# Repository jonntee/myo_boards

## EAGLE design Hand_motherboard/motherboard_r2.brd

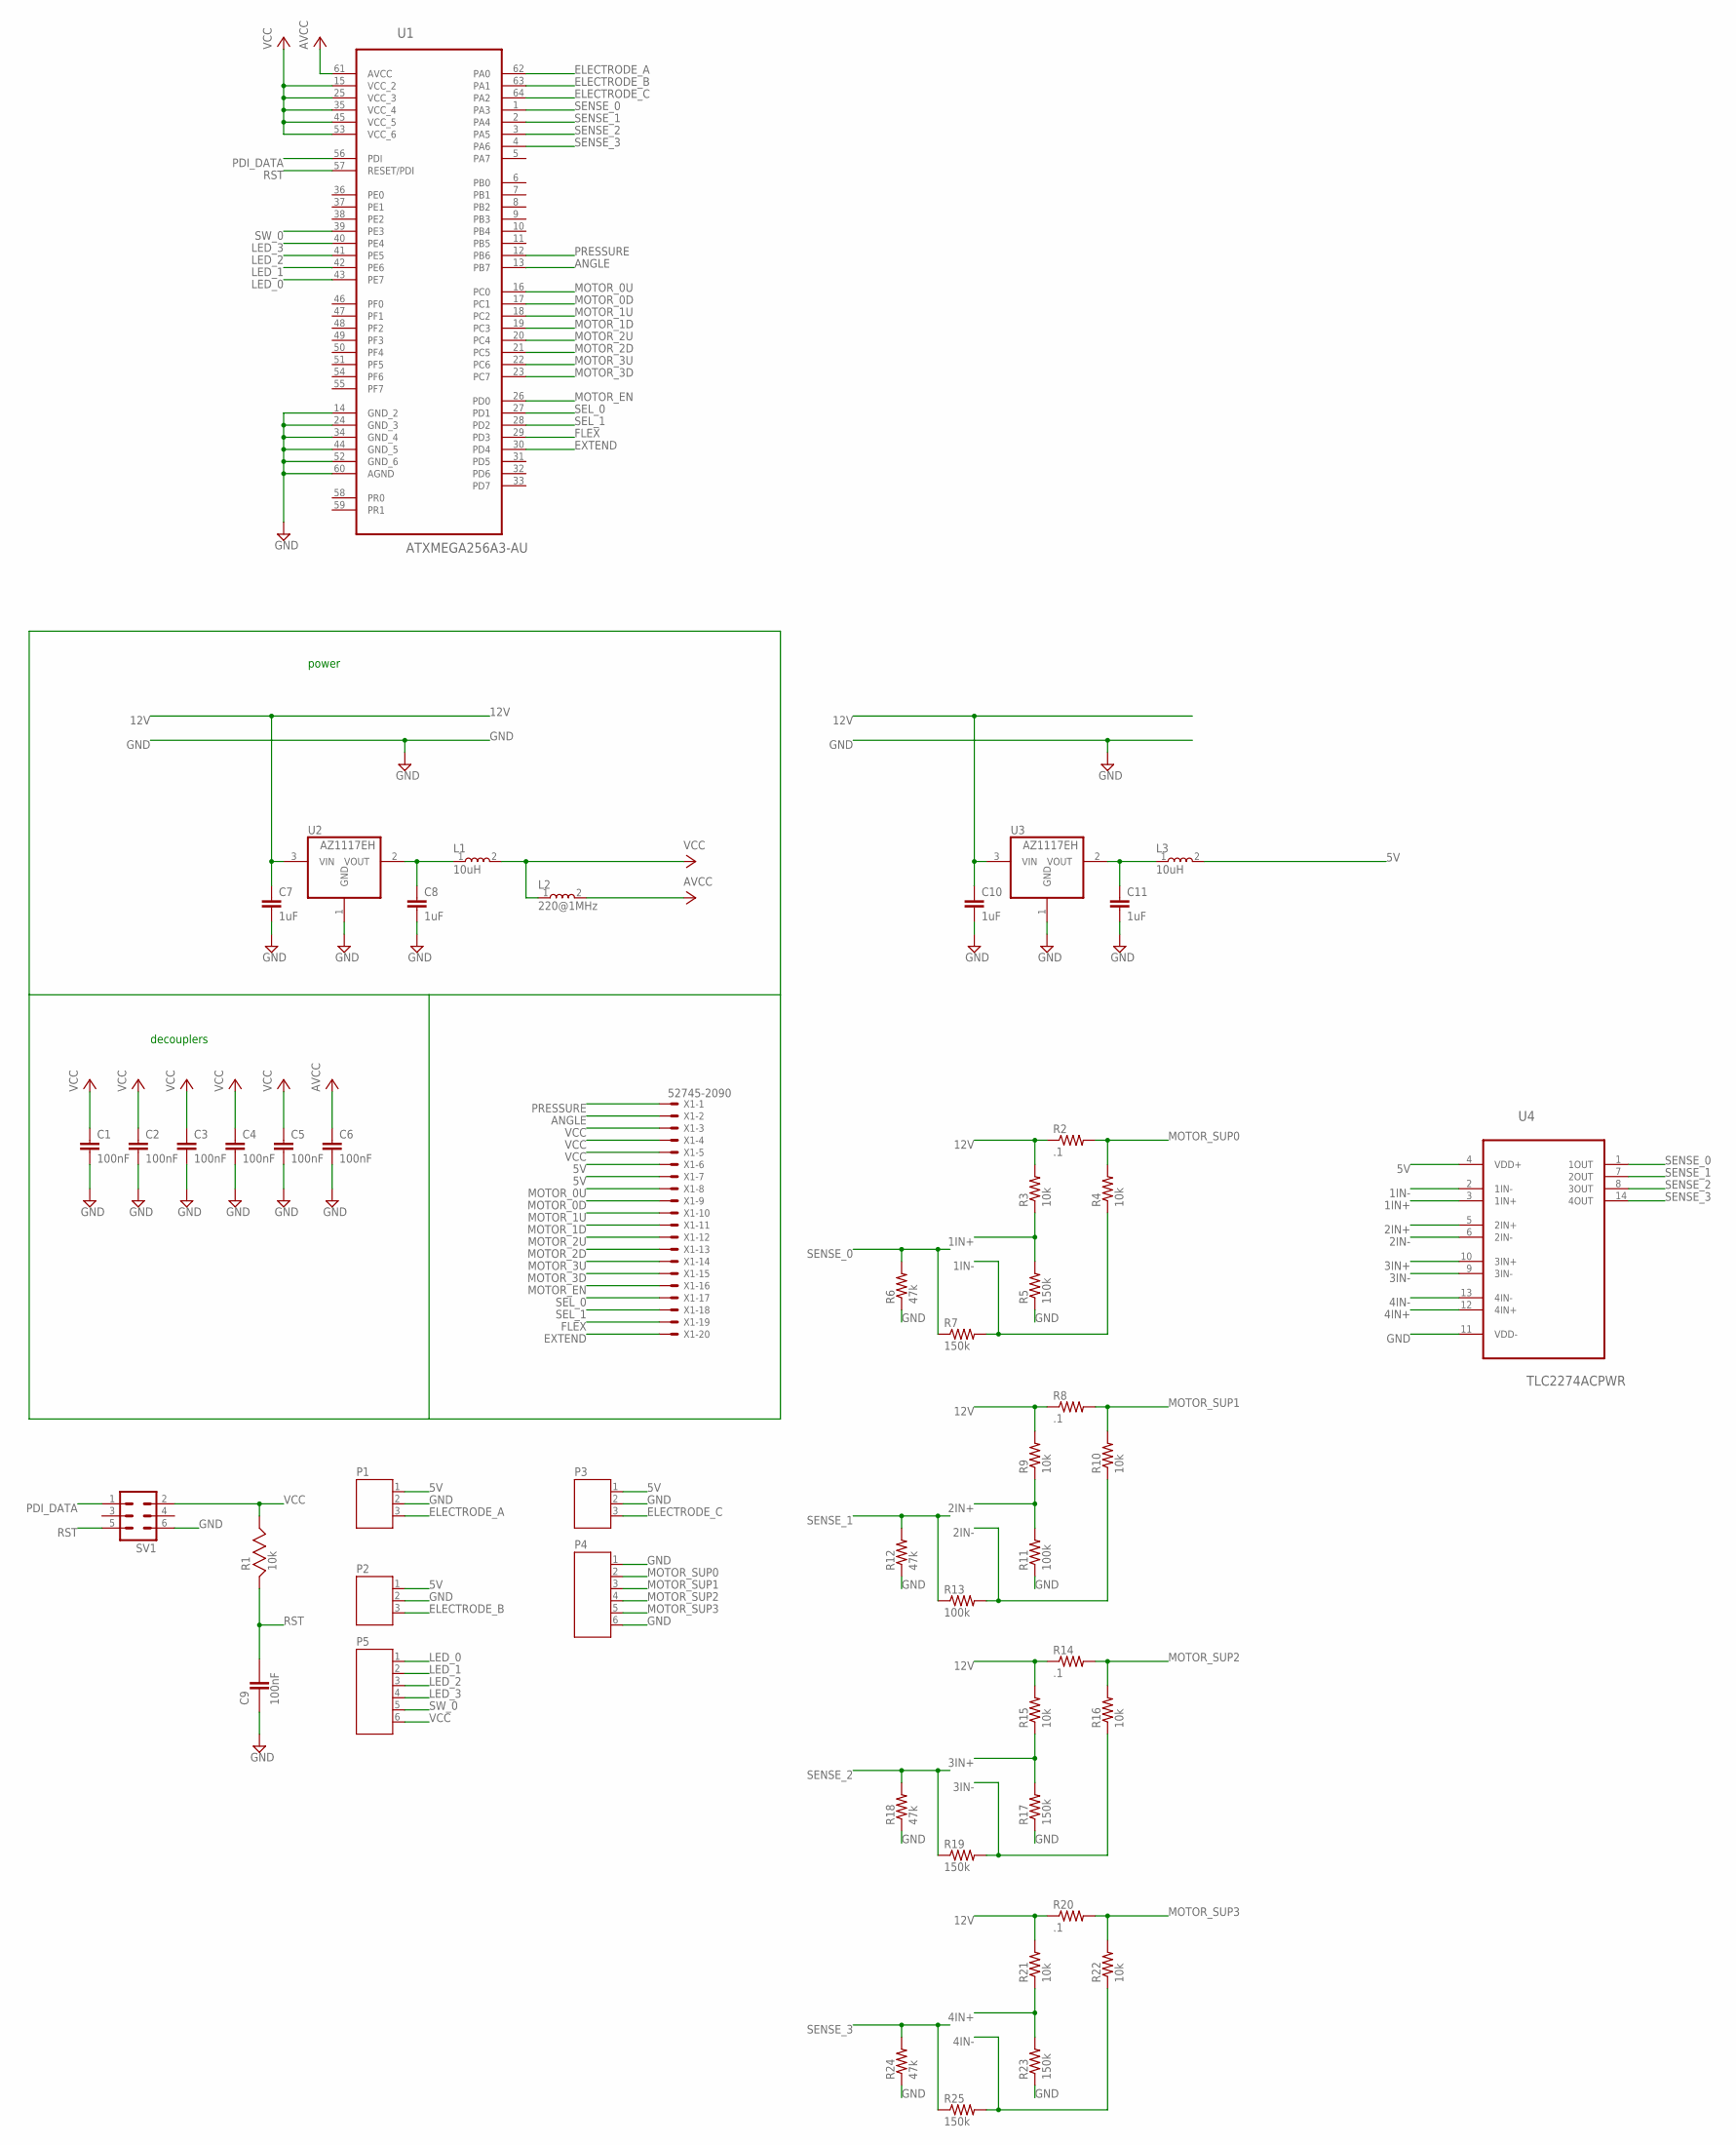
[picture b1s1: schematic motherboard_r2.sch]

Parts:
C1, C2, C3, C4, C5, C6: 100nF; C0603
C7, C8, C10, C11: 1uF; C0603
C9: 100nF; CC0603KRX7R8BB105_CAPC1608X90
L1, L3: 10uH; 0805
L2: 220@1MHz; 0805
P1, P2, P3: JST-PH3
P4, P5: JST-PH6
R1: 10k; CRCW060310K0FKEA_RESC1608X55
R2, R8, R14, R20: .1; R0603
R3, R4, R9, R10, R15, R16, R21, R22: 10k; R0603
R5, R7, R17, R19, R23, R25: 150k; R0603
R6, R12, R18, R24: 47k; R0603
R11, R13: 100k; R0603
SV1: MA03-2
U1: ATXMEGA256A3-AU; QFP80P1600X1600X120-64N
U2, U3: AZ1117EH; SOT230P700X160-4N
U4: TLC2274ACPWR; SOP65P640X120-14N
X1: 52745-2090

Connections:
1IN+: R3.1, R5.2, U4.3 (1IN+)
1IN-: R4.1, R7.2, U4.2 (1IN-)
2IN+: R9.1, R11.2, U4.5 (2IN+)
2IN-: R10.1, R13.2, U4.6 (2IN-)
3IN+: R15.1, R17.2, U4.10 (3IN+)
3IN-: R16.1, R19.2, U4.9 (3IN-)
4IN+: R21.1, R23.2, U4.12 (4IN+)
4IN-: R22.1, R25.2, U4.13 (4IN-)
5V: L3.2, P1.1, P2.1, P3.1, U4.4 (VDD+), X1.6, X1.7
12V: C7.1, C10.1, R2.1, R3.2, R8.1, R9.2, R14.1, R15.2, R20.1, R21.2, U2.3 (VIN), U3.3 (VIN)
ANGLE: U1.13 (PB7), X1.2
AVCC: C6.1, L2.2, U1.61 (AVCC)
ELECTRODE_A: P1.3, U1.62 (PA0)
ELECTRODE_B: P2.3, U1.63 (PA1)
ELECTRODE_C: P3.3, U1.64 (PA2)
EXTEND: U1.30 (PD4), X1.20
FLEX: U1.29 (PD3), X1.19
GND: C1.2, C2.2, C3.2, C4.2, C5.2, C6.2, C7.2, C8.2, C9.1, C10.2, C11.2, P1.2, P2.2, P3.2, P4.1, P4.6, R5.1, R6.1, R11.1, R12.1, R17.1, R18.1, R23.1, R24.1, SV1.6, U1.14 (GND_2), U1.24 (GND_3), U1.34 (GND_4), U1.44 (GND_5), U1.52 (GND_6), U1.60 (AGND), U2.1 (GND), U3.1 (GND), U4.11 (VDD-)
LED_0: P5.1, U1.43 (PE7)
LED_1: P5.2, U1.42 (PE6)
LED_2: P5.3, U1.41 (PE5)
LED_3: P5.4, U1.40 (PE4)
MOTOR_0D: U1.17 (PC1), X1.9
MOTOR_0U: U1.16 (PC0), X1.8
MOTOR_1D: U1.19 (PC3), X1.11
MOTOR_1U: U1.18 (PC2), X1.10
MOTOR_2D: U1.21 (PC5), X1.13
MOTOR_2U: U1.20 (PC4), X1.12
MOTOR_3D: U1.23 (PC7), X1.15
MOTOR_3U: U1.22 (PC6), X1.14
MOTOR_EN: U1.26 (PD0), X1.16
MOTOR_SUP0: P4.2, R2.2, R4.2
MOTOR_SUP1: P4.3, R8.2, R10.2
MOTOR_SUP2: P4.4, R14.2, R16.2
MOTOR_SUP3: P4.5, R20.2, R22.2
unnamed: C8.1, L1.1, U2.2 (VOUT)
unnamed: C11.1, L3.1, U3.2 (VOUT)
PDI_DATA: SV1.1, U1.56 (PDI)
PRESSURE: U1.12 (PB6), X1.1
RST: C9.2, R1.1, SV1.5, U1.57 (RESET/PDI)
SEL_0: U1.27 (PD1), X1.17
SEL_1: U1.28 (PD2), X1.18
SENSE_0: R6.2, R7.1, U1.1 (PA3), U4.1 (1OUT)
SENSE_1: R12.2, R13.1, U1.2 (PA4), U4.7 (2OUT)
SENSE_2: R18.2, R19.1, U1.3 (PA5), U4.8 (3OUT)
SENSE_3: R24.2, R25.1, U1.4 (PA6), U4.14 (4OUT)
SW_0: P5.5, U1.39 (PE3)
VCC: C1.1, C2.1, C3.1, C4.1, C5.1, L1.2, L2.1, P5.6, R1.2, SV1.2, U1.15 (VCC_2), U1.25 (VCC_3), U1.35 (VCC_4), U1.45 (VCC_5), U1.53 (VCC_6), X1.3, X1.4, X1.5

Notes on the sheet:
decouplers
power

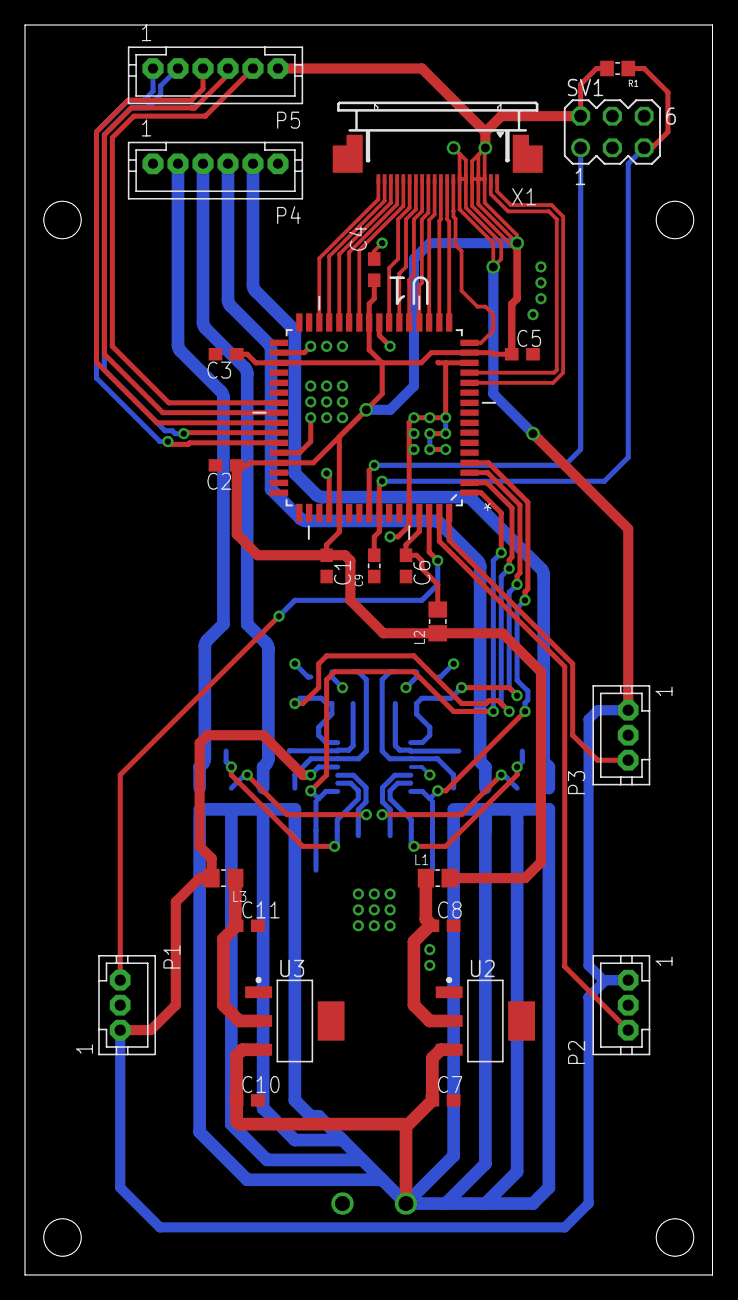
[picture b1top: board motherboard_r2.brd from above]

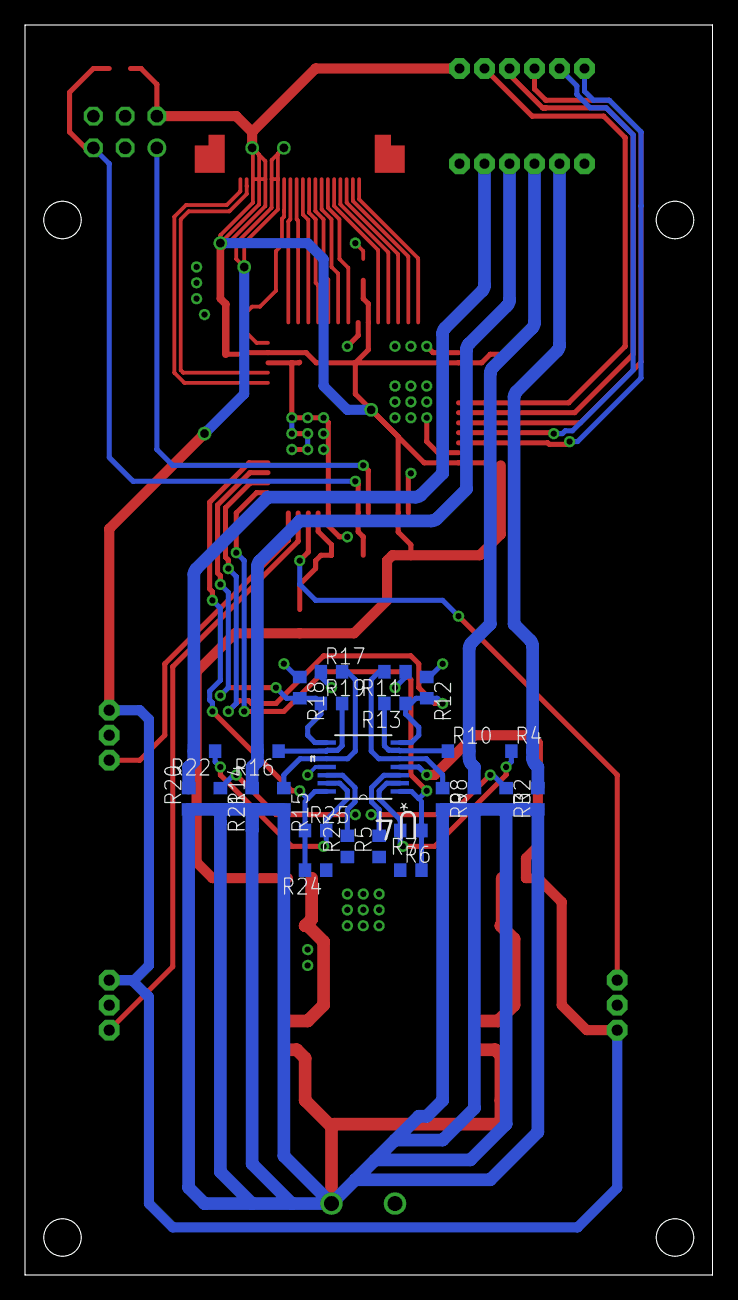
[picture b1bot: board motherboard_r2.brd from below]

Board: 2 copper layers, 55.0 x 100.0 mm, 50 parts (25 on the bottom side), 48 nets.

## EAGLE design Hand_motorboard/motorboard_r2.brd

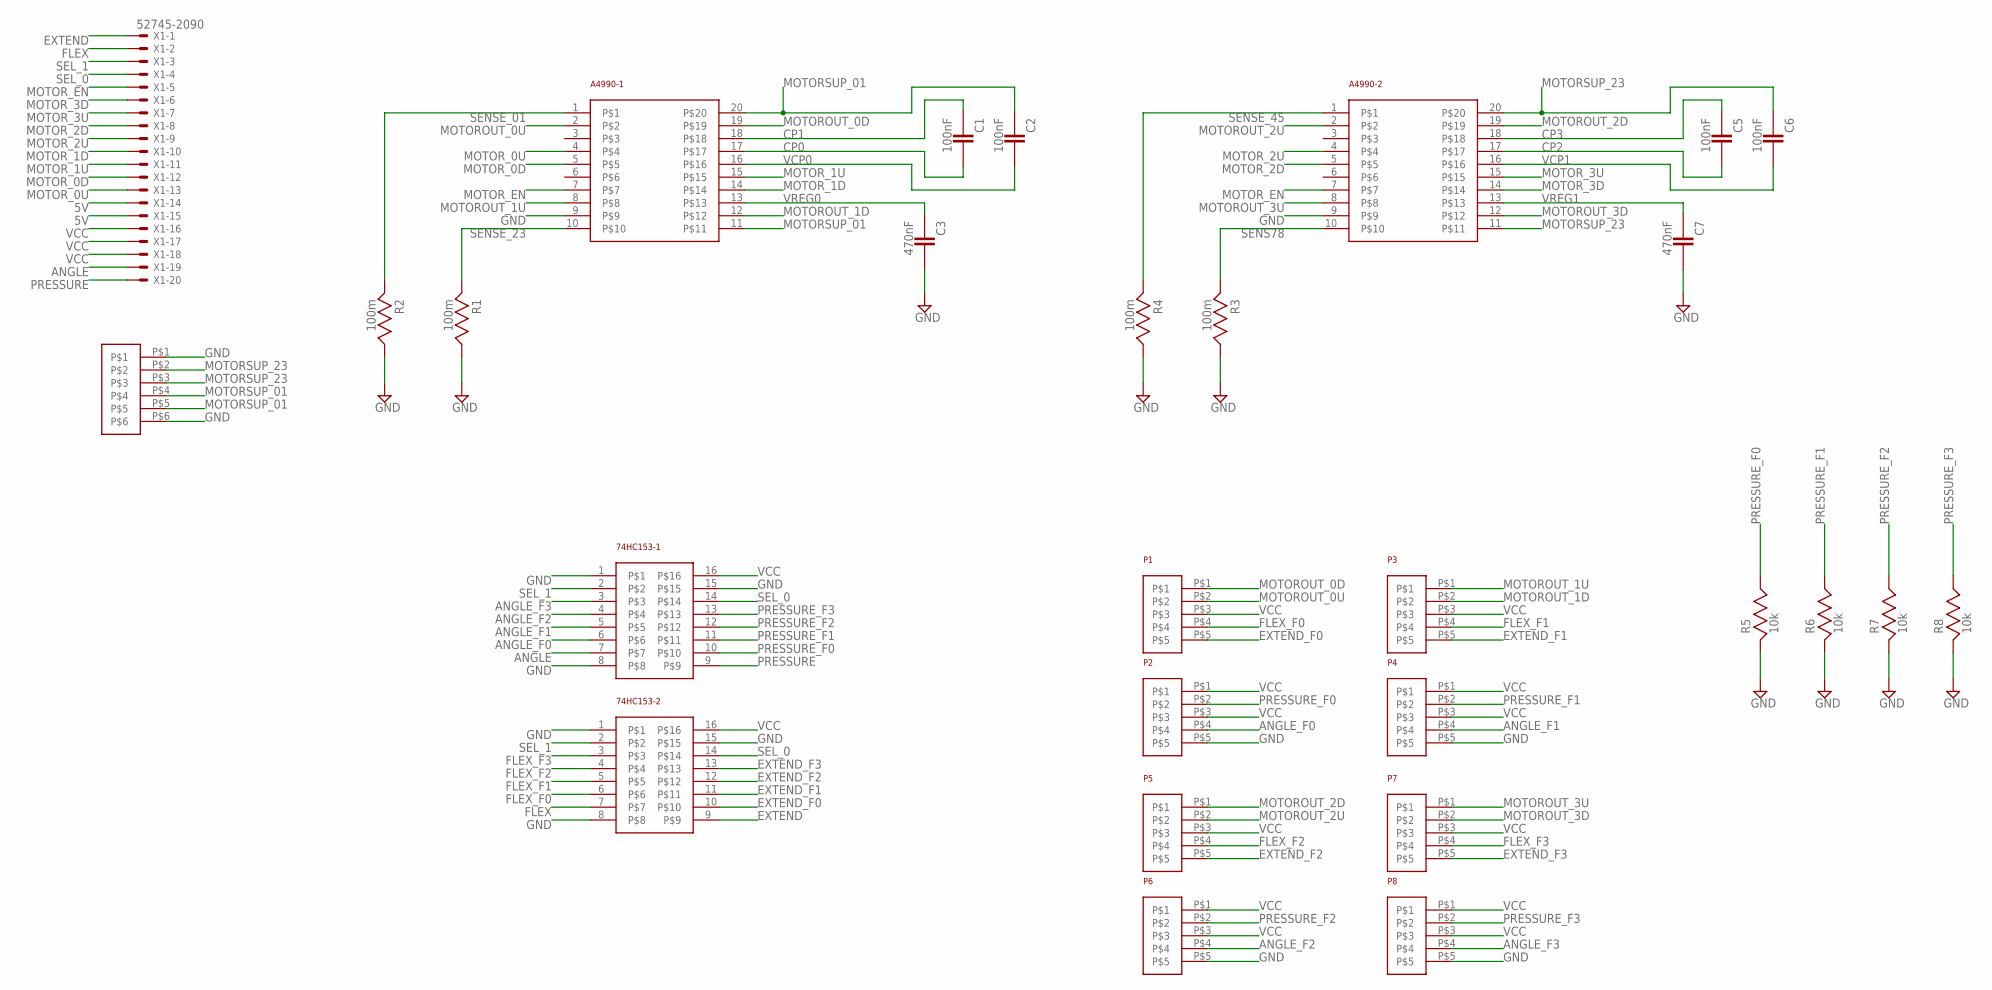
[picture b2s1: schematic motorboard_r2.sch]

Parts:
74HC153-1, 74HC153-2: 74HC153; SO-16_S-M
A4990-1, A4990-2: A4990
C1, C2, C5, C6: 100nF; CC0603KRX7R9BB104_CAPC1608X90
C3, C7: 470nF; CC0603KRX7R9BB104_CAPC1608X90
P1, P2, P3, P4, P5, P6, P7, P8: S5B-PH-SM4-TB
R1, R2, R3, R4: 100m; CRCW06031K00FKEA_RESC1608X55
R5, R6, R7, R8: 10k; CRCW06031K00FKEA_RESC1608X55
U$1: PH-SM4-6
X1: 52745-2090

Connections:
5V: X1.14, X1.15
ANGLE: 74HC153-1.7, X1.19
ANGLE_F0: 74HC153-1.6, P2.P$4
ANGLE_F1: 74HC153-1.5, P4.P$4
ANGLE_F2: 74HC153-1.4, P6.P$4
ANGLE_F3: 74HC153-1.3, P8.P$4
CP0: A4990-1.17, C1.2
CP1: A4990-1.18, C1.1
CP2: A4990-2.17, C5.2
CP3: A4990-2.18, C5.1
EXTEND: 74HC153-2.9, X1.1
EXTEND_F0: 74HC153-2.10, P1.P$5
EXTEND_F1: 74HC153-2.11, P3.P$5
EXTEND_F2: 74HC153-2.12, P5.P$5
EXTEND_F3: 74HC153-2.13, P7.P$5
FLEX: 74HC153-2.7, X1.2
FLEX_F0: 74HC153-2.6, P1.P$4
FLEX_F1: 74HC153-2.5, P3.P$4
FLEX_F2: 74HC153-2.4, P5.P$4
FLEX_F3: 74HC153-2.3, P7.P$4
GND: 74HC153-1.1, 74HC153-1.8, 74HC153-1.15, 74HC153-2.1, 74HC153-2.8, 74HC153-2.15, A4990-1.9, A4990-2.9, C3.2, C7.2, P2.P$5, P4.P$5, P6.P$5, P8.P$5, R1.2, R2.2, R3.2, R4.2, R5.1, R6.1, R7.1, R8.1, U$1.P$1, U$1.P$6
MOTOROUT_0D: A4990-1.19, P1.P$1
MOTOROUT_0U: A4990-1.2, P1.P$2
MOTOROUT_1D: A4990-1.12, P3.P$2
MOTOROUT_1U: A4990-1.8, P3.P$1
MOTOROUT_2D: A4990-2.19, P5.P$1
MOTOROUT_2U: A4990-2.2, P5.P$2
MOTOROUT_3D: A4990-2.12, P7.P$2
MOTOROUT_3U: A4990-2.8, P7.P$1
MOTORSUP_01: A4990-1.11, A4990-1.20, C2.1, U$1.P$4, U$1.P$5
MOTORSUP_23: A4990-2.11, A4990-2.20, C6.1, U$1.P$2, U$1.P$3
MOTOR_0D: A4990-1.5, X1.12
MOTOR_0U: A4990-1.4, X1.13
MOTOR_1D: A4990-1.14, X1.10
MOTOR_1U: A4990-1.15, X1.11
MOTOR_2D: A4990-2.5, X1.8
MOTOR_2U: A4990-2.4, X1.9
MOTOR_3D: A4990-2.14, X1.6
MOTOR_3U: A4990-2.15, X1.7
MOTOR_EN: A4990-1.7, A4990-2.7, X1.5
PRESSURE: 74HC153-1.9, X1.20
PRESSURE_F0: 74HC153-1.10, P2.P$2, R5.2
PRESSURE_F1: 74HC153-1.11, P4.P$2, R6.2
PRESSURE_F2: 74HC153-1.12, P6.P$2, R7.2
PRESSURE_F3: 74HC153-1.13, P8.P$2, R8.2
SEL_0: 74HC153-1.14, 74HC153-2.14, X1.4
SEL_1: 74HC153-1.2, 74HC153-2.2, X1.3
SENS78: A4990-2.10, R3.1
SENSE_01: A4990-1.1, R2.1
SENSE_23: A4990-1.10, R1.1
SENSE_45: A4990-2.1, R4.1
VCC: 74HC153-1.16, 74HC153-2.16, P1.P$3, P2.P$1, P2.P$3, P3.P$3, P4.P$1, P4.P$3, P5.P$3, P6.P$1, P6.P$3, P7.P$3, P8.P$1, P8.P$3, X1.16, X1.17, X1.18
VCP0: A4990-1.16, C2.2
VCP1: A4990-2.16, C6.2
VREG0: A4990-1.13, C3.1
VREG1: A4990-2.13, C7.1

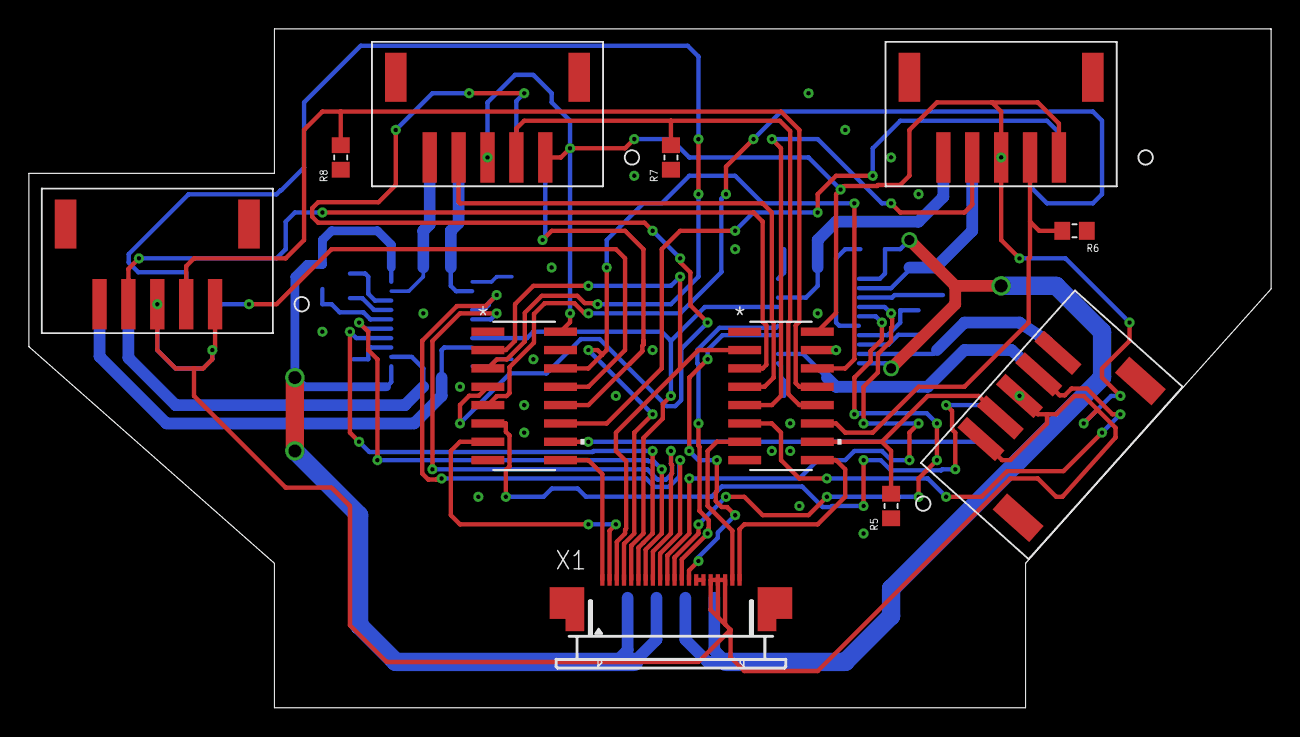
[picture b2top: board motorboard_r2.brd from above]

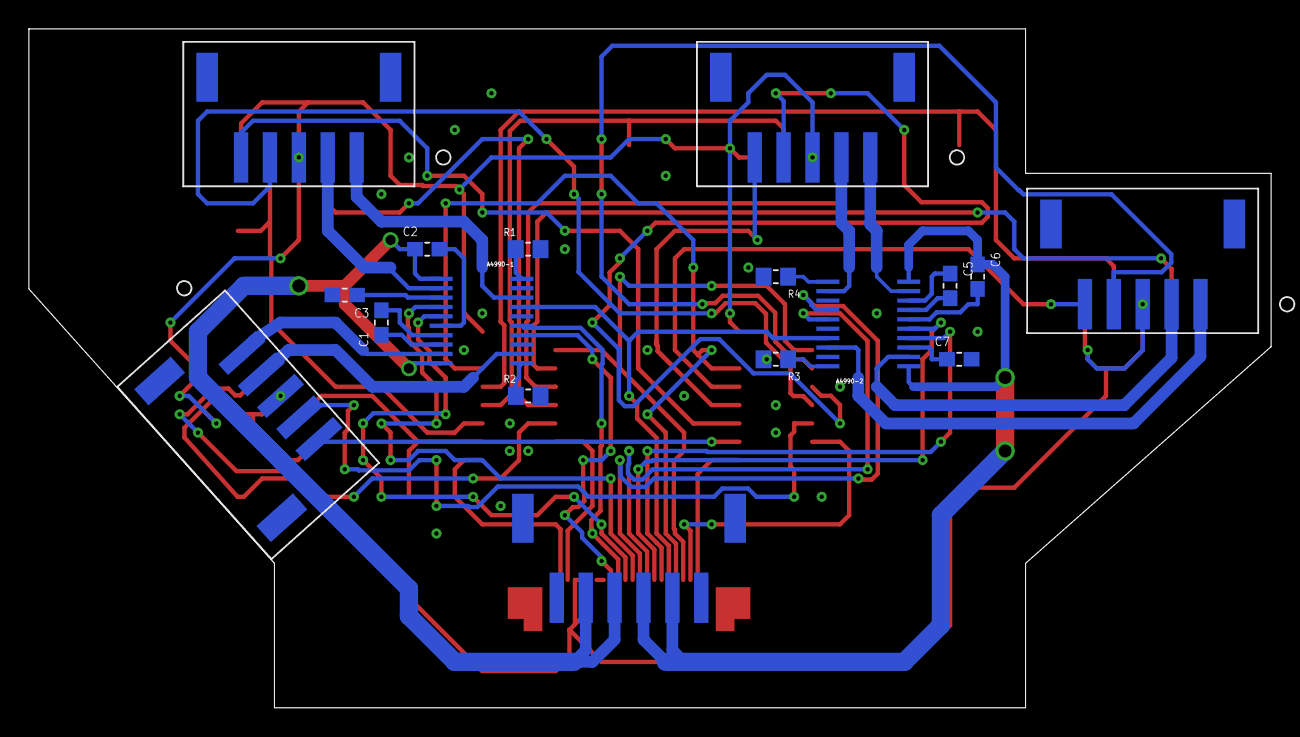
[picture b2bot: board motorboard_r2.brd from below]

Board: 2 copper layers, 86.0 x 47.0 mm, 28 parts (17 on the bottom side), 56 nets.

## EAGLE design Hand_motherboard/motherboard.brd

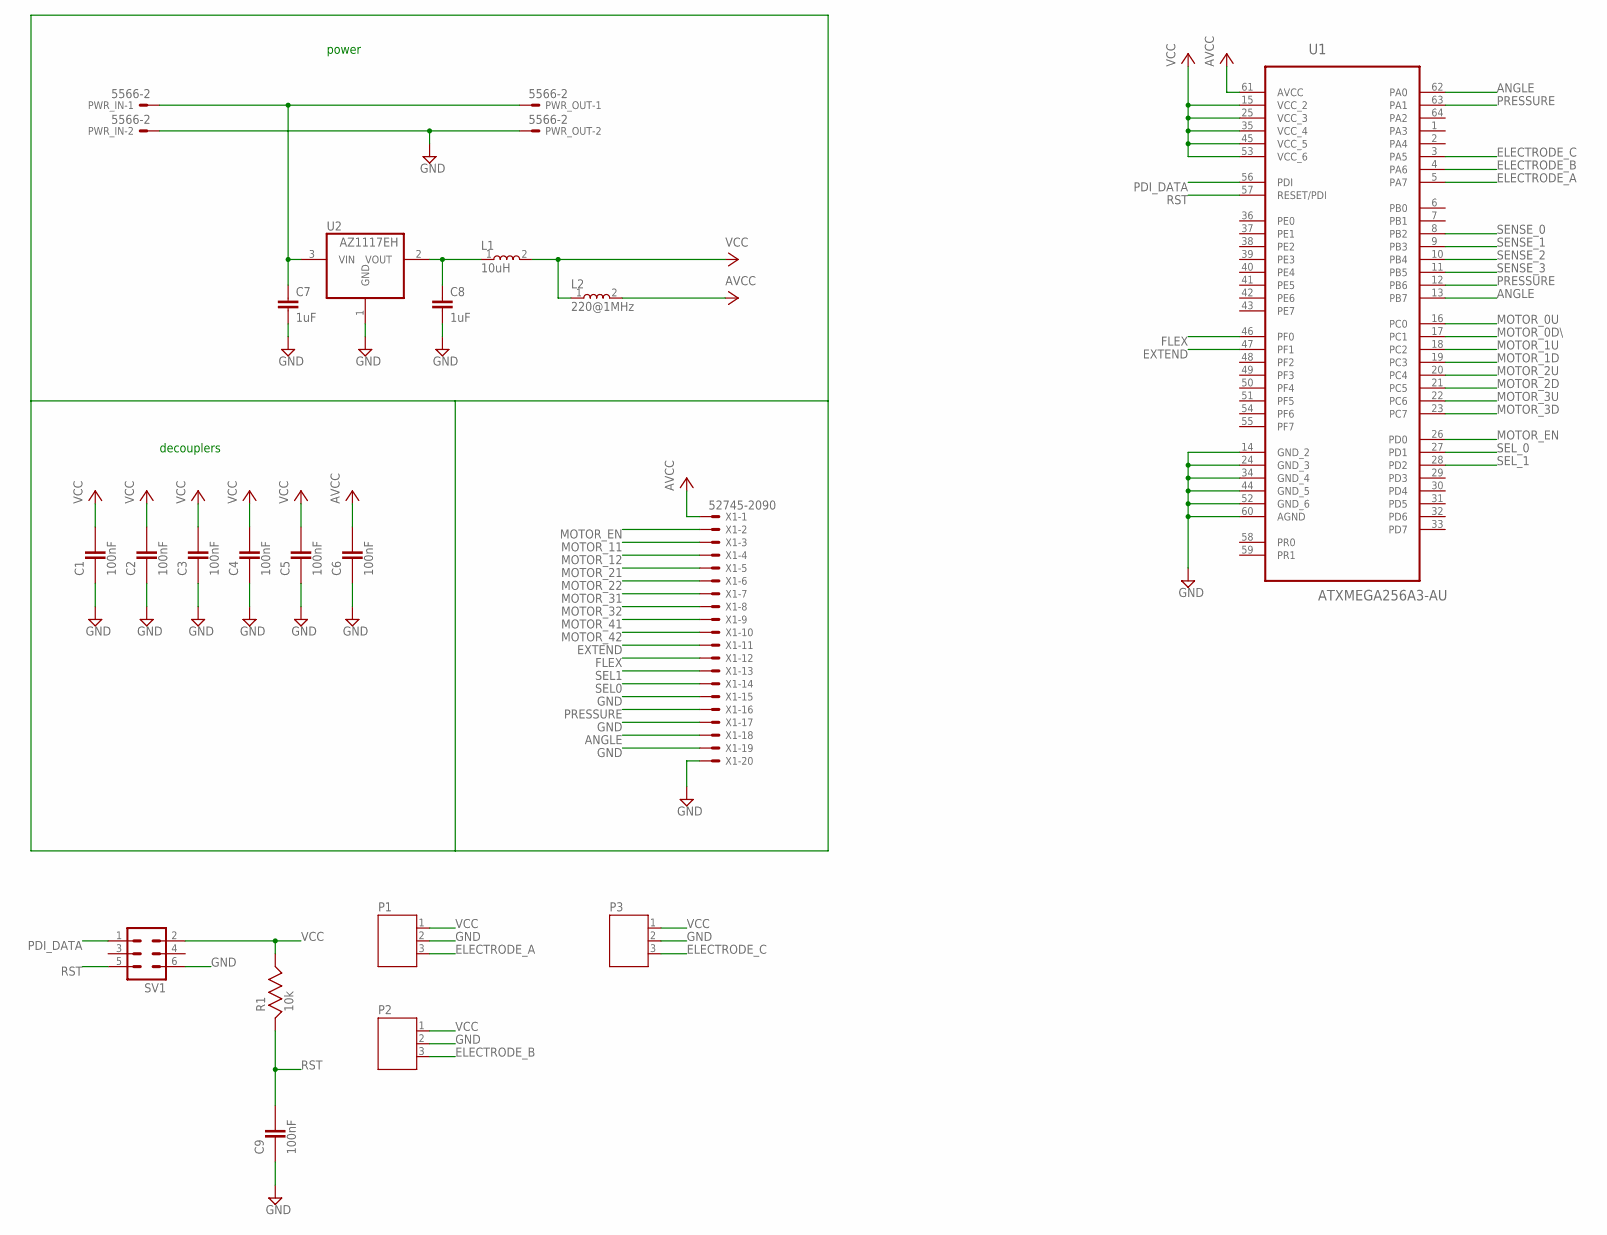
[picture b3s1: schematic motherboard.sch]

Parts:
C1, C2, C3, C4, C5, C6: 100nF; 0508
C7, C8: 1uF; C0805
C9: 100nF; CC0603KRX7R8BB105_CAPC1608X90
L1: 10uH; 0805
L2: 220@1MHz; 0805
P1, P2, P3: JST-PH3
PWR_IN: 5566-2
PWR_OUT: 5566-2
R1: 10k; CRCW060310K0FKEA_RESC1608X55
SV1: MA03-2
U1: ATXMEGA256A3-AU; QFP80P1600X1600X120-64N
U2: AZ1117EH; SOT230P700X160-4N
X1: 52745-2090

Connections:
ANGLE: U1.13 (PB7), U1.62 (PA0), X1.18
AVCC: C6.P$1 (1), L2.2, U1.61 (AVCC), X1.1
BAT+: C7.1, PWR_IN.1, PWR_OUT.1, U2.3 (VIN)
ELECTRODE_A: P1.3, U1.5 (PA7)
ELECTRODE_B: P2.3, U1.4 (PA6)
ELECTRODE_C: P3.3, U1.3 (PA5)
EXTEND: U1.47 (PF1), X1.11
FLEX: U1.46 (PF0), X1.12
GND: C1.P$2 (2), C2.P$2 (2), C3.P$2 (2), C4.P$2 (2), C5.P$2 (2), C6.P$2 (2), C7.2, C8.2, C9.1, P1.2, P2.2, P3.2, PWR_IN.2, PWR_OUT.2, SV1.6, U1.14 (GND_2), U1.24 (GND_3), U1.34 (GND_4), U1.44 (GND_5), U1.52 (GND_6), U1.60 (AGND), U2.1 (GND), X1.15, X1.17, X1.19, X1.20
MOTOR_0D\: U1.17 (PC1)
MOTOR_0U: U1.16 (PC0)
MOTOR_1D: U1.19 (PC3)
MOTOR_1U: U1.18 (PC2)
MOTOR_2D: U1.21 (PC5)
MOTOR_2U: U1.20 (PC4)
MOTOR_3D: U1.23 (PC7)
MOTOR_3U: U1.22 (PC6)
MOTOR_11: X1.3
MOTOR_12: X1.4
MOTOR_21: X1.5
MOTOR_22: X1.6
MOTOR_31: X1.7
MOTOR_32: X1.8
MOTOR_41: X1.9
MOTOR_42: X1.10
MOTOR_EN: U1.26 (PD0), X1.2
unnamed: C8.1, L1.1, U2.2 (VOUT)
PDI_DATA: SV1.1, U1.56 (PDI)
PRESSURE: U1.12 (PB6), U1.63 (PA1), X1.16
RST: C9.2, R1.1, SV1.5, U1.57 (RESET/PDI)
SEL0: X1.14
SEL1: X1.13
SEL_0: U1.27 (PD1)
SEL_1: U1.28 (PD2)
SENSE_0: U1.8 (PB2)
SENSE_1: U1.9 (PB3)
SENSE_2: U1.10 (PB4)
SENSE_3: U1.11 (PB5)
VCC: C1.P$1 (1), C2.P$1 (1), C3.P$1 (1), C4.P$1 (1), C5.P$1 (1), L1.2, L2.1, P1.1, P2.1, P3.1, R1.2, SV1.2, U1.15 (VCC_2), U1.25 (VCC_3), U1.35 (VCC_4), U1.45 (VCC_5), U1.53 (VCC_6)

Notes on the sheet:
decouplers
power

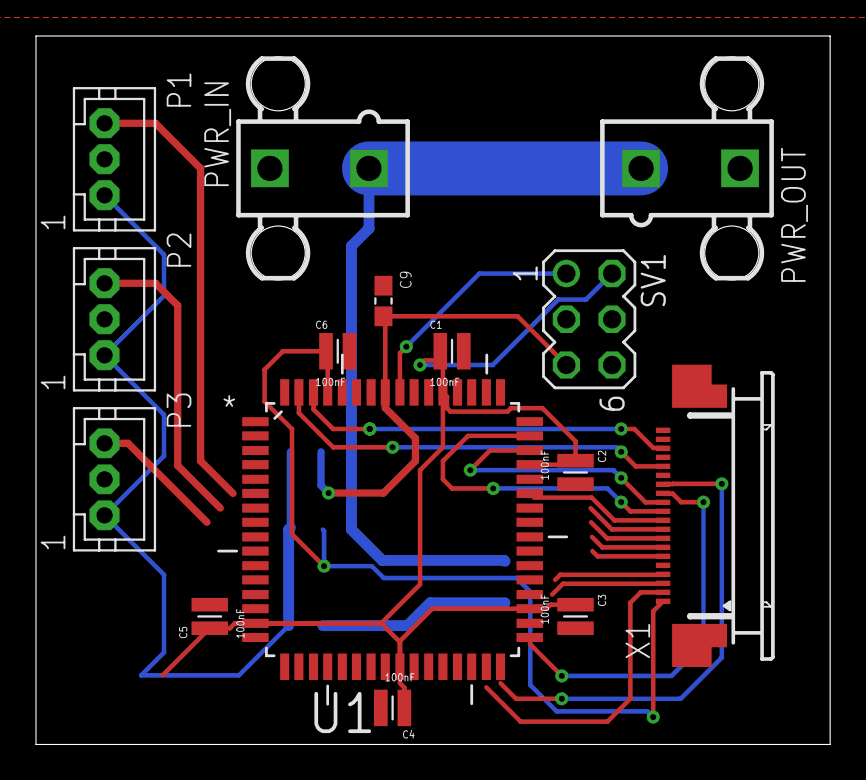
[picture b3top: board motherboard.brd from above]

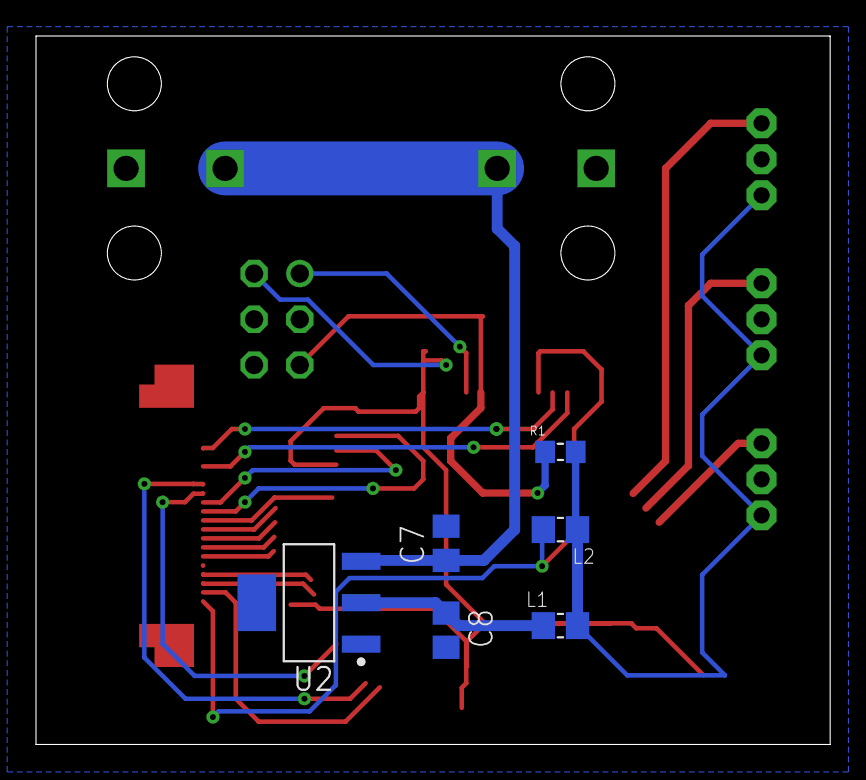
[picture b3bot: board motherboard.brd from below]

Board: 2 copper layers, 44.1 x 39.4 mm, 21 parts (6 on the bottom side), 15 nets.

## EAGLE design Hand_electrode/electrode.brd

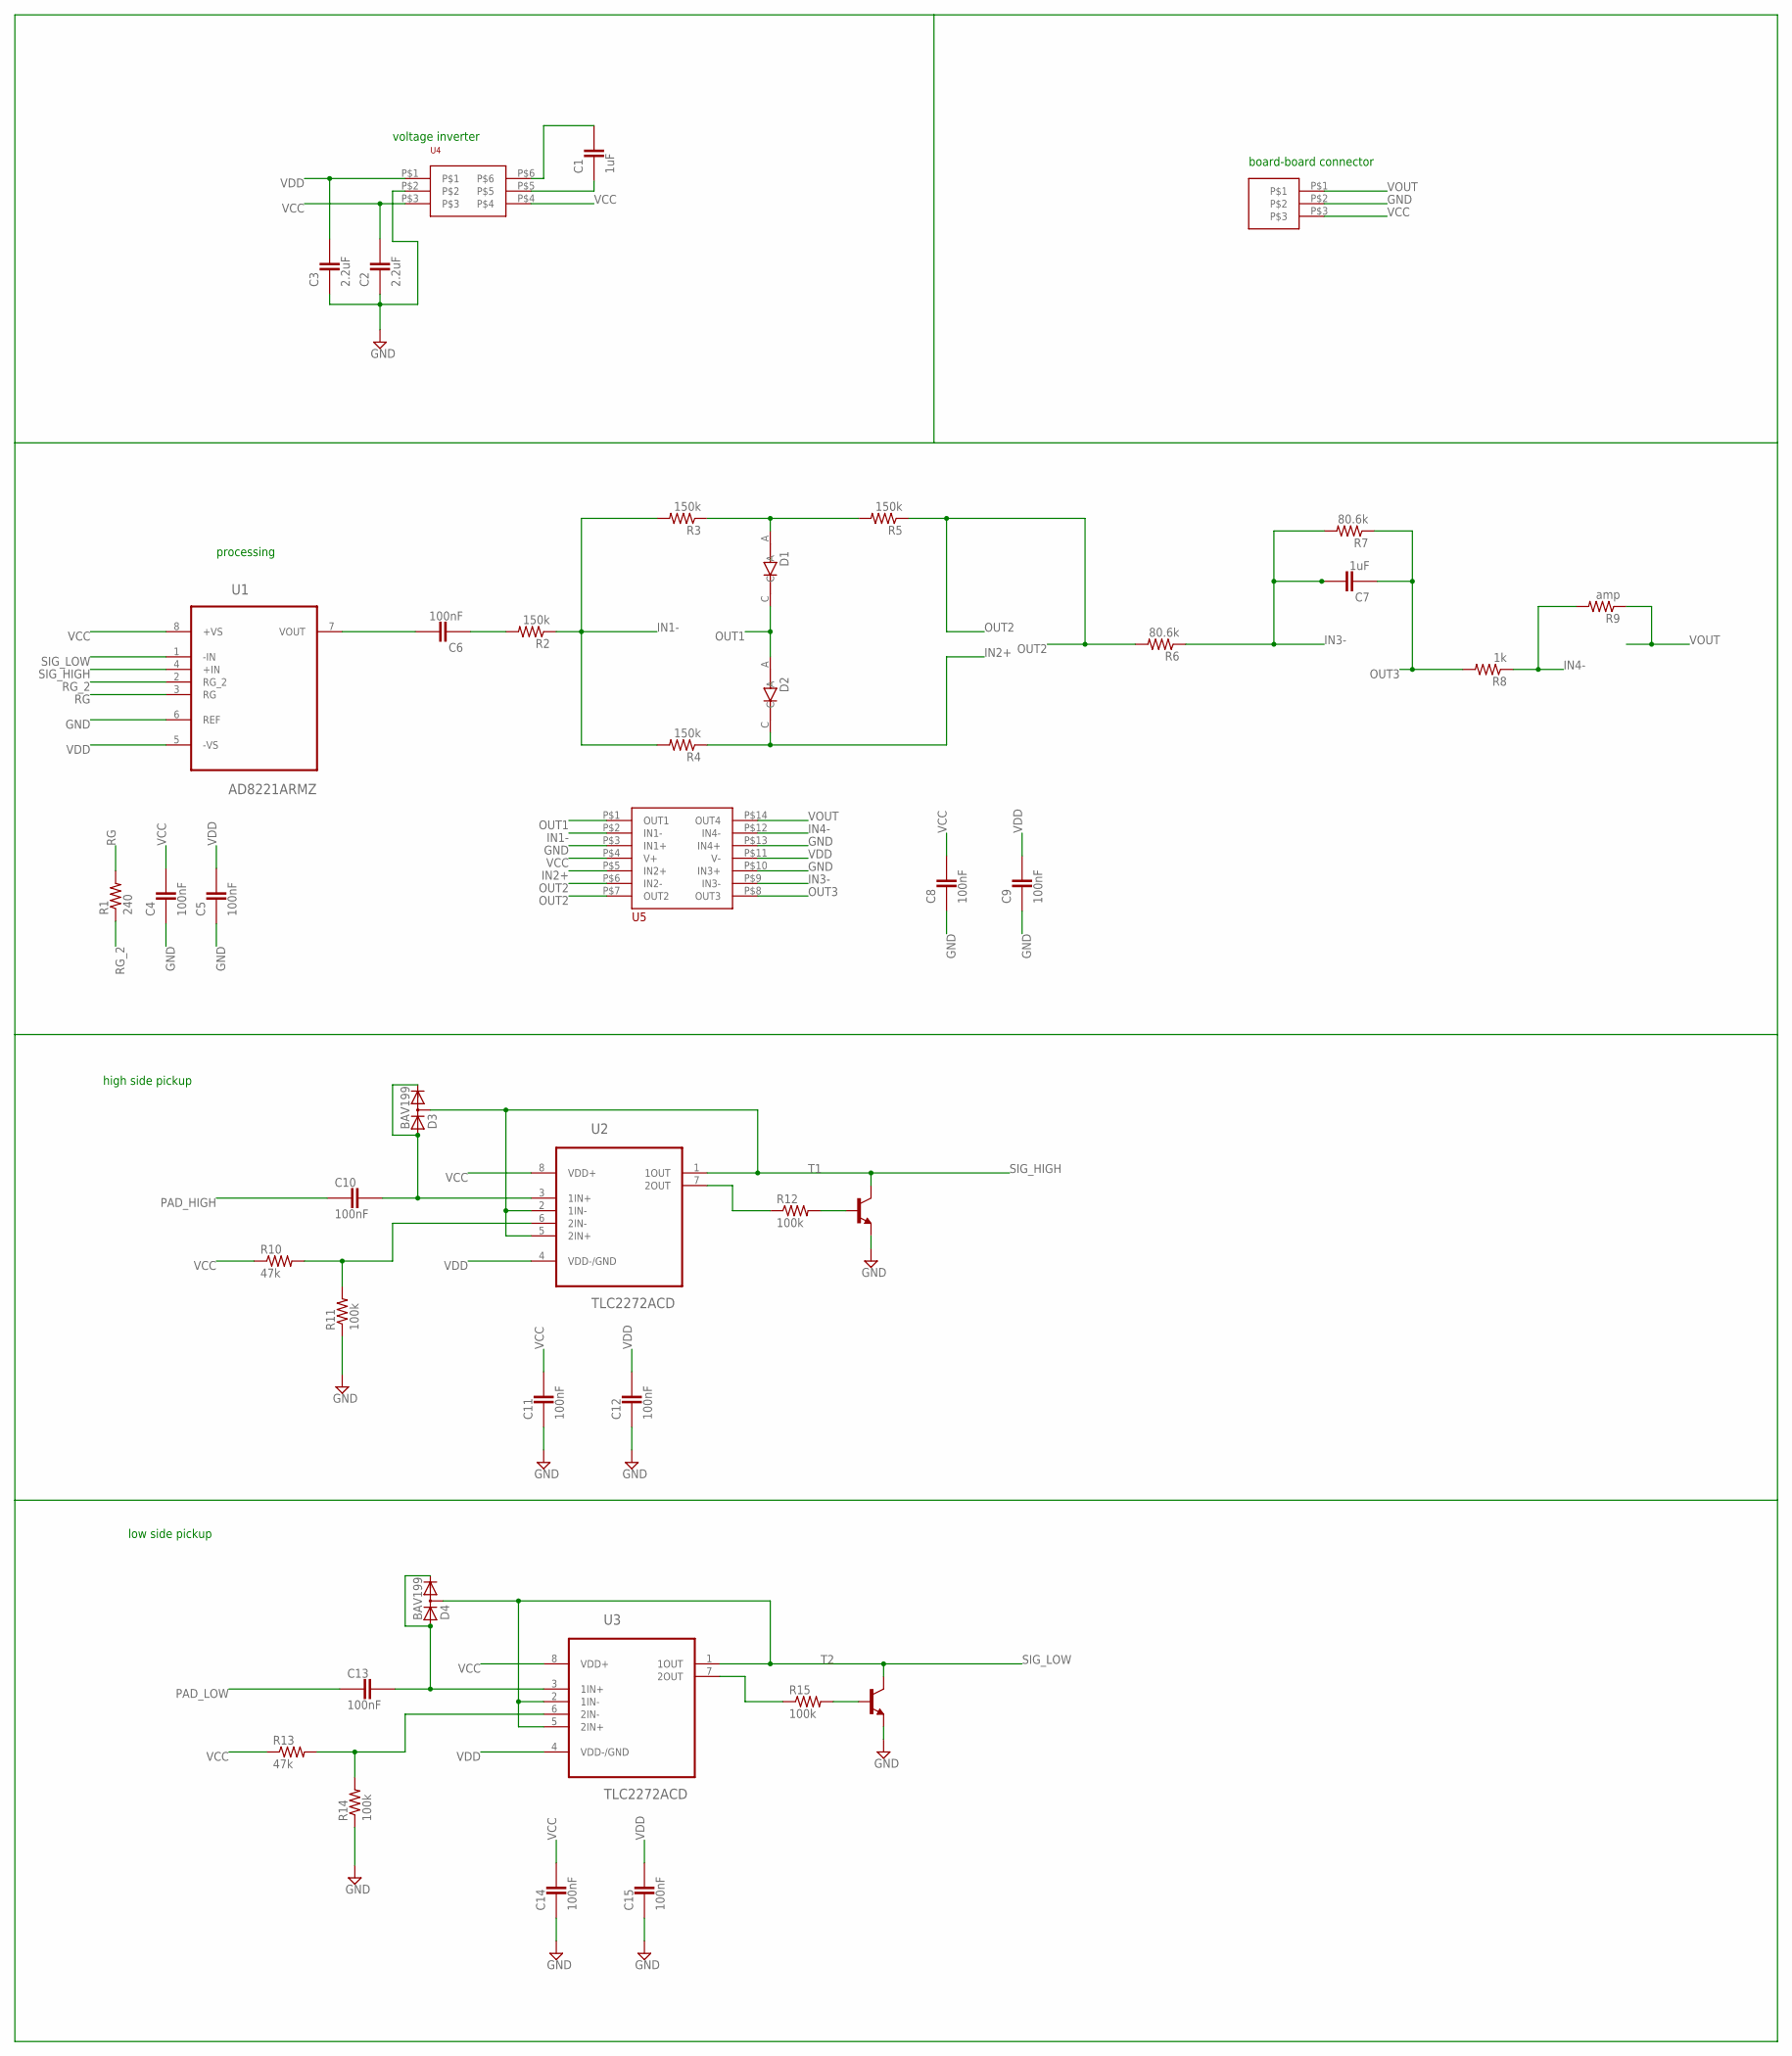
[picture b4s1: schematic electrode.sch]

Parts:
C1, C7: 1uF; C0603C100C5GACTU_CAPC1608X90
C2, C3: 2.2uF; C0603C100C5GACTU_CAPC1608X90
C4, C5, C6, C8, C9, C10, C11, C12, C13, C14, C15: 100nF; C0603C100C5GACTU_CAPC1608X90
D1, D2: 1N4148WS-7-F; SOD2513X120N
D3, D4: BAV199; SOT23
R1: 240; R0603
R2, R3, R4, R5: 150k; R0603
R6, R7: 80.6k; R0603
R8: 1k; R0603
R9: amp; R0603
R10, R13: 47k; R0603
R11, R12, R14, R15: 100k; R0603
T1, T2: MMBT2222ALT1-NPN-SOT23-BEC; SOT23-BEC
U1: AD8221ARMZ; SOP65P490X110-8N
U2, U3: TLC2272ACD; SOIC127P600X175-8N
U4: LM2776; LM2776-SO
U5: TL084; TL084-TSSOP
U$2: B3B-PH-SM4

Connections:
CFLY+: C1.2, U4.P$5
CFLY-: C1.1, U4.P$6
GND: C2.2, C3.2, C4.2, C5.2, C8.2, C9.2, C11.2, C12.2, C14.2, C15.2, R11.1, R14.1, T1.E, T2.E, U1.6 (REF), U4.P$2, U5.P$3 (IN1+), U5.P$10 (IN3+), U5.P$13 (IN4+), U$2.P$2
IN1-: R2.1, R3.2, R4.2, U5.P$2 (IN1-)
IN2+: D2.C, R4.1, U5.P$5 (IN2+)
IN3-: C7.1, R6.1, R7.2, U5.P$9 (IN3-)
IN4-: R8.1, R9.2, U5.P$12 (IN4-)
unnamed: C6.1, U1.7 (VOUT)
unnamed: C6.2, R2.2
unnamed: R13.2, R14.2, U3.6 (2IN-)
unnamed: D1.A, R3.1, R5.2
unnamed: C13.1, D4.1 (A), D4.2 (C), U3.3 (1IN+)
unnamed: R10.2, R11.2, U2.6 (2IN-)
unnamed: C10.1, D3.1 (A), D3.2 (C), U2.3 (1IN+)
unnamed: R12.1, U2.7 (2OUT)
unnamed: R12.2, T1.B
unnamed: R15.1, U3.7 (2OUT)
unnamed: R15.2, T2.B
OUT1: D1.C, D2.A, U5.P$1 (OUT1)
OUT2: R5.1, R6.2, U5.P$6 (IN2-), U5.P$7 (OUT2)
OUT3: C7.2, R7.1, R8.2, U5.P$8 (OUT3)
PAD_HIGH: C10.2
PAD_LOW: C13.2
RG: R1.2, U1.3 (RG)
RG_2: R1.1, U1.2 (RG_2)
SIG_HIGH: D3.3 (AC), T1.C, U1.4 (+IN), U2.1 (1OUT), U2.2 (1IN-), U2.5 (2IN+)
SIG_LOW: D4.3 (AC), T2.C, U1.1 (-IN), U3.1 (1OUT), U3.2 (1IN-), U3.5 (2IN+)
VCC: C2.1, C4.1, C8.1, C11.1, C14.1, R10.1, R13.1, U1.8 (+VS), U2.8 (VDD+), U3.8 (VDD+), U4.P$3, U4.P$4, U5.P$4 (V+), U$2.P$3
VDD: C3.1, C5.1, C9.1, C12.1, C15.1, U1.5 (-VS), U2.4 (VDD-/GND), U3.4 (VDD-/GND), U4.P$1, U5.P$11 (V-)
VOUT: R9.1, U5.P$14 (OUT4), U$2.P$1

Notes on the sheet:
board-board connector
voltage inverter
high side pickup
low side pickup
processing

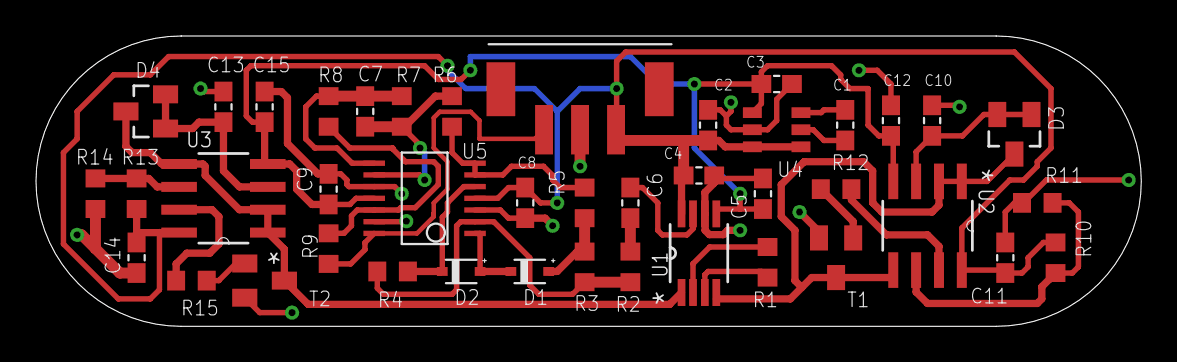
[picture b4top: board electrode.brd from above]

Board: 2 copper layers, 61.4 x 16.1 mm, 42 parts (0 on the bottom side), 28 nets.

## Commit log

2017-05-07 initial push
2017-05-07 git ignore
2017-05-07 I think I figured out how gitignore works*
2017-05-19 Create Button
2017-05-20 finished motorboard
2017-07-18 many changes
